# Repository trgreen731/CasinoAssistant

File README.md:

# The Odds Booster

This project is created by Marco Rojas, Jack Arndt, and Tim Green within UIUC ECE 445.

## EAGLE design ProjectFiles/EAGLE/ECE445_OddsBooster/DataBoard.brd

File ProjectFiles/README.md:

### File Type Notes
.dia files are used within the diagram software Dia

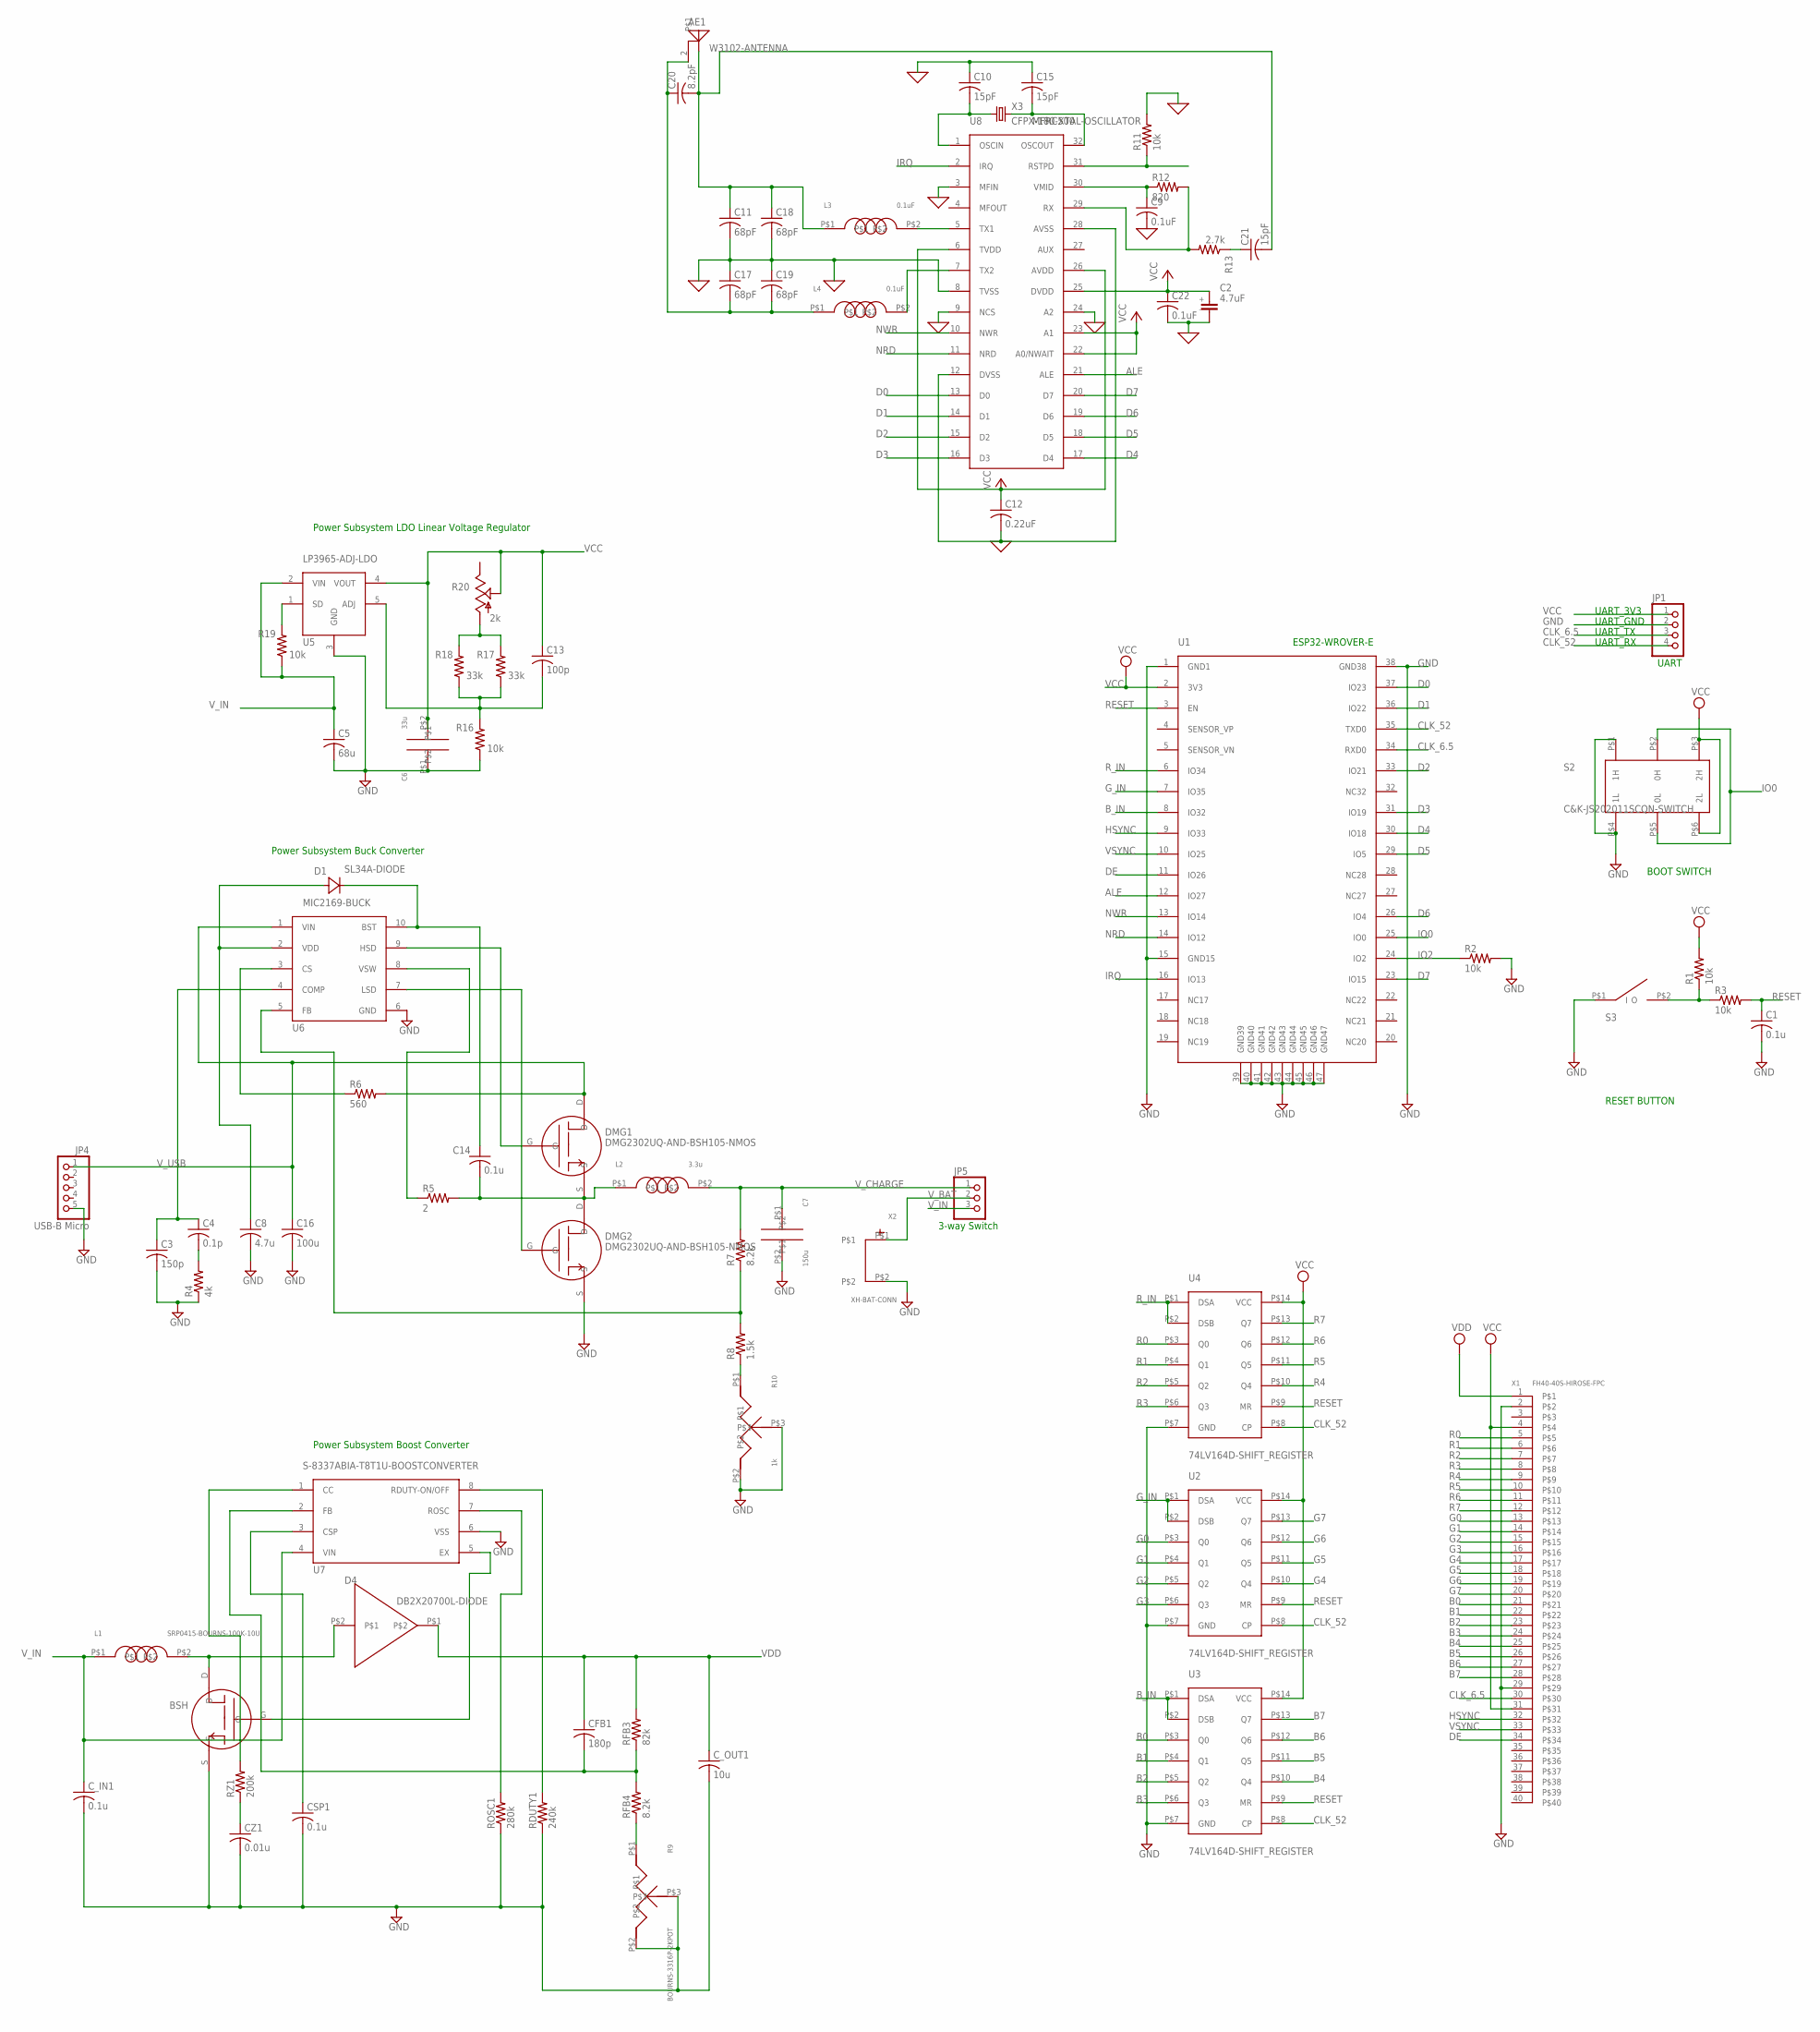
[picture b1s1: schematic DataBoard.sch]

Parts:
AE1: W3102-ANTENNA
BSH: DMG2302UQ-AND-BSH105-NMOS
C1, C14: 0.1u; C0805
C2: 4.7uF; 865080640004-ELECTROLYTIC-CAP
C3: 150p; C0805
C4: 0.1p; C0603
C5: 68u; C1206
C6: 33u; NEMCO-33U-TANT-CAP
C7: 150u; KEMET-T491-150U-TANT
C8: 4.7u; C0603
C9, C22: 0.1uF; C0805
C10, C15, C21: 15pF; C0805K
C11, C17, C18, C19: 68pF; C0805K
C12: 0.22uF; C0402
C13: 100p; C0805
C16: 100u; C1210
C20: 8.2pF; C0402
CFB1: 180p; C0805
CSP1: 0.1u; C0805
CZ1: 0.01u; C0805
C_IN1: 0.1u; C0805
C_OUT1: 10u; C0805
D1: SL34A-DIODE
D4: DB2X20700L-DIODE
DMG1, DMG2: DMG2302UQ-AND-BSH105-NMOS
JP1: PINHD-1X4; 1X04
JP4: USB-B Micro; 1X05
JP5: PINHD-1X3; 1X03
L1: SRP0415-BOURNS-100K-10U
L2: 3.3u; SRP0415-BOURNS-100K-10U
L3, L4: 0.1uF; SRP0415-BOURNS-100K-10U
R1, R2, R3, R11, R16, R19: 10k; R0805
R4: 4k; R0805
R5: 2; R0805
R6: 560; R0805
R7: 8.2k; R0805
R8: 1.5k; R0805
R9: BOURNS-3316P-2KPOT
R10: 1k; BOURNS-3316P-2KPOT
R12: 820; R0805
R13: 2.7k; R0805
R17, R18: 33k; R0805
R20: 2k; 3223G
RDUTY1: 240k; R0805
RFB3: 82k; R0805
RFB4: 8.2k; R0805
ROSC1: 280k; R0805
RZ1: 200k; R0805
S2: C&K-JS202011SCQN-SWITCH
S3: C&K-PTS636SL43SMTRLFS-PUSHBUTTON
U1: ESP32-WROVER-E
U2, U3, U4: 74LV164D-SHIFT_REGISTER
U5: LP3965-ADJ-LDO
U6: MIC2169-BUCK
U7: S-8337ABIA-T8T1U-BOOSTCONVERTER
U8: MFRC500
X1: FH40-40S-HIROSE-FPC
X2: XH-BAT-CONN
X3: CFPX-180-XTAL-OSCILLATOR

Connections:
0: C2.2- (2), C9.2, C10.1, C11.2, C12.2, C15.1, C17.1, C18.2, C19.1, C22.2, R11.2, U8.3 (MFIN), U8.8 (TVSS), U8.9 (NCS), U8.12 (DVSS), U8.24 (A2), U8.28 (AVSS)
ALE: U1.12 (IO27), U8.21 (ALE)
B0: U3.P$3 (Q0), X1.21
B1: U3.P$4 (Q1), X1.22
B2: U3.P$5 (Q2), X1.23
B3: U3.P$6 (Q3), X1.24
B4: U3.P$10 (Q4), X1.25
B5: U3.P$11 (Q5), X1.26
B6: U3.P$12 (Q6), X1.27
B7: U3.P$13 (Q7), X1.28
B_IN: U1.8 (IO32), U3.P$1 (DSA), U3.P$2 (DSB)
CLK_6.5: JP1.3, U1.34 (RXD0), X1.30
CLK_52: JP1.4, U1.35 (TXD0), U2.P$8 (CP), U3.P$8 (CP), U4.P$8 (CP)
D0: U1.37 (IO23), U8.13 (D0)
D1: U1.36 (IO22), U8.14 (D1)
D2: U1.33 (IO21), U8.15 (D2)
D3: U1.31 (IO19), U8.16 (D3)
D4: U1.30 (IO18), U8.17 (D4)
D5: U1.29 (IO5), U8.18 (D5)
D6: U1.26 (IO4), U8.19 (D6)
D7: U1.23 (IO15), U8.20 (D7)
DE: U1.11 (IO26), X1.34
EN: R1.1, R3.1, S3.P$2 (O)
G0: U2.P$3 (Q0), X1.13
G1: U2.P$4 (Q1), X1.14
G2: U2.P$5 (Q2), X1.15
G3: U2.P$6 (Q3), X1.16
G4: U2.P$10 (Q4), X1.17
G5: U2.P$11 (Q5), X1.18
G6: U2.P$12 (Q6), X1.19
G7: U2.P$13 (Q7), X1.20
GND: BSH.S, C1.2, C3.2, C5.2, C6.P$1, C7.P$2, C8.2, C16.2, CSP1.2, CZ1.2, C_IN1.2, C_OUT1.2, DMG2.S, JP1.2, JP4.5, R2.2, R4.1, R9.P$2, R9.P$3, R10.P$2, R10.P$3, R16.1, RDUTY1.1, ROSC1.1, S2.P$1 (1H), S2.P$4 (1L), S3.P$1 (I), U1.1 (GND1), U1.15 (GND15), U1.38 (GND38), U1.39 (GND39), U1.40 (GND40), U1.41 (GND41), U1.42 (GND42), U1.43 (GND43), U1.44 (GND44), U1.45 (GND45), U1.46 (GND46), U1.47 (GND47), U2.P$7 (GND), U3.P$7 (GND), U4.P$7 (GND), U5.3 (GND), U6.6 (GND), U7.6 (VSS), X1.2, X1.29, X2.P$2
G_IN: U1.7 (IO35), U2.P$1 (DSA), U2.P$2 (DSB)
HSYNC: U1.9 (IO33), X1.32
IO0: S2.P$2 (0H), S2.P$5 (0L), U1.25 (IO0)
IO2: R2.1, U1.24 (IO2)
IRQ: U1.16 (IO13), U8.2 (IRQ)
unnamed: C14.2, DMG1.S, DMG2.D, L2.P$1, R5.2
unnamed: C8.1, D1.1 (A), U6.2 (VDD)
unnamed: R5.1, U6.8 (VSW)
unnamed: C14.1, D1.2 (C), U6.10 (BST)
unnamed: C10.2, U8.1 (OSCIN), X3.1
unnamed: C15.2, U8.32 (OSCOUT), X3.3 (2)
unnamed: R11.1, U8.31 (RSTPD)
unnamed: C9.1, R12.1, U8.30 (VMID)
unnamed: R12.2, R13.2, U8.29 (RX)
unnamed: C21.1, R13.1
unnamed: L3.P$2, U8.5 (TX1)
unnamed: L4.P$2, U8.7 (TX2)
unnamed: AE1.1, C11.1, C18.1, C20.2, C21.2, L3.P$1
unnamed: AE1.2, C17.2, C19.2, C20.1, L4.P$1
unnamed: C13.2, R16.2, R17.1, R18.1, U5.5 (ADJ)
unnamed: R19.2, U5.1 (SD)
unnamed: R17.2, R18.2, R20.1 (A)
unnamed: DMG1.G, U6.9 (HSD)
unnamed: DMG2.G, U6.7 (LSD)
unnamed: R6.1, U6.3 (CS)
unnamed: C4.2, R4.2
unnamed: C3.1, C4.1, U6.4 (COMP)
unnamed: R7.1, R8.2, U6.5 (FB)
unnamed: R8.1, R10.P$1
unnamed: CSP1.1, U7.3 (CSP)
unnamed: BSH.G, U7.5 (EX)
unnamed: CZ1.1, RZ1.1
unnamed: RZ1.2, U7.1 (CC)
unnamed: CFB1.2, RFB3.1, RFB4.2, U7.2 (FB)
unnamed: ROSC1.2, U7.7 (ROSC)
unnamed: RDUTY1.2, U7.8 (RDUTY-ON/OFF)
unnamed: R9.P$1, RFB4.1
unnamed: BSH.D, D4.P$2, L1.P$2
NRD: U1.14 (IO12), U8.11 (NRD)
NWR: U1.13 (IO14), U8.10 (NWR)
R0: U4.P$3 (Q0), X1.5
R1: U4.P$4 (Q1), X1.6
R2: U4.P$5 (Q2), X1.7
R3: U4.P$6 (Q3), X1.8
R4: U4.P$10 (Q4), X1.9
R5: U4.P$11 (Q5), X1.10
R6: U4.P$12 (Q6), X1.11
R7: U4.P$13 (Q7), X1.12
RESET: C1.1, R3.2, U1.3 (EN), U2.P$9 (MR), U3.P$9 (MR), U4.P$9 (MR)
R_IN: U1.6 (IO34), U4.P$1 (DSA), U4.P$2 (DSB)
VCC: C2.1+ (1), C6.P$2, C12.1, C13.1, C22.1, JP1.1, R1.2, R20.2 (S), S2.P$3 (2H), S2.P$6 (2L), U1.2 (3V3), U2.P$14 (VCC), U3.P$14 (VCC), U4.P$14 (VCC), U5.4 (VOUT), U8.6 (TVDD), U8.22 (A0/NWAIT), U8.23 (A1), U8.25 (DVDD), U8.26 (AVDD), X1.4, X1.31
VDD: CFB1.1, C_OUT1.1, D4.P$1, RFB3.2, X1.1
VSYNC: U1.10 (IO25), X1.33
V_BAT: JP5.2, X2.P$1
V_CHARGE: C7.P$1, JP5.1, L2.P$2, R7.2
V_IN: C5.1, C_IN1.1, JP5.3, L1.P$1, R19.1, U5.2 (VIN), U7.4 (VIN)
V_USB: C16.1, DMG1.D, JP4.1, R6.2, U6.1 (VIN)

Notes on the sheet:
UART
RESET BUTTON
BOOT SWITCH
UART_RX
UART_TX
ESP32-WROVER-E
UART_3V3
UART_GND
Power Subsystem LDO Linear Voltage Regulator
Power Subsystem Buck Converter
Power Subsystem Boost Converter
3-way Switch

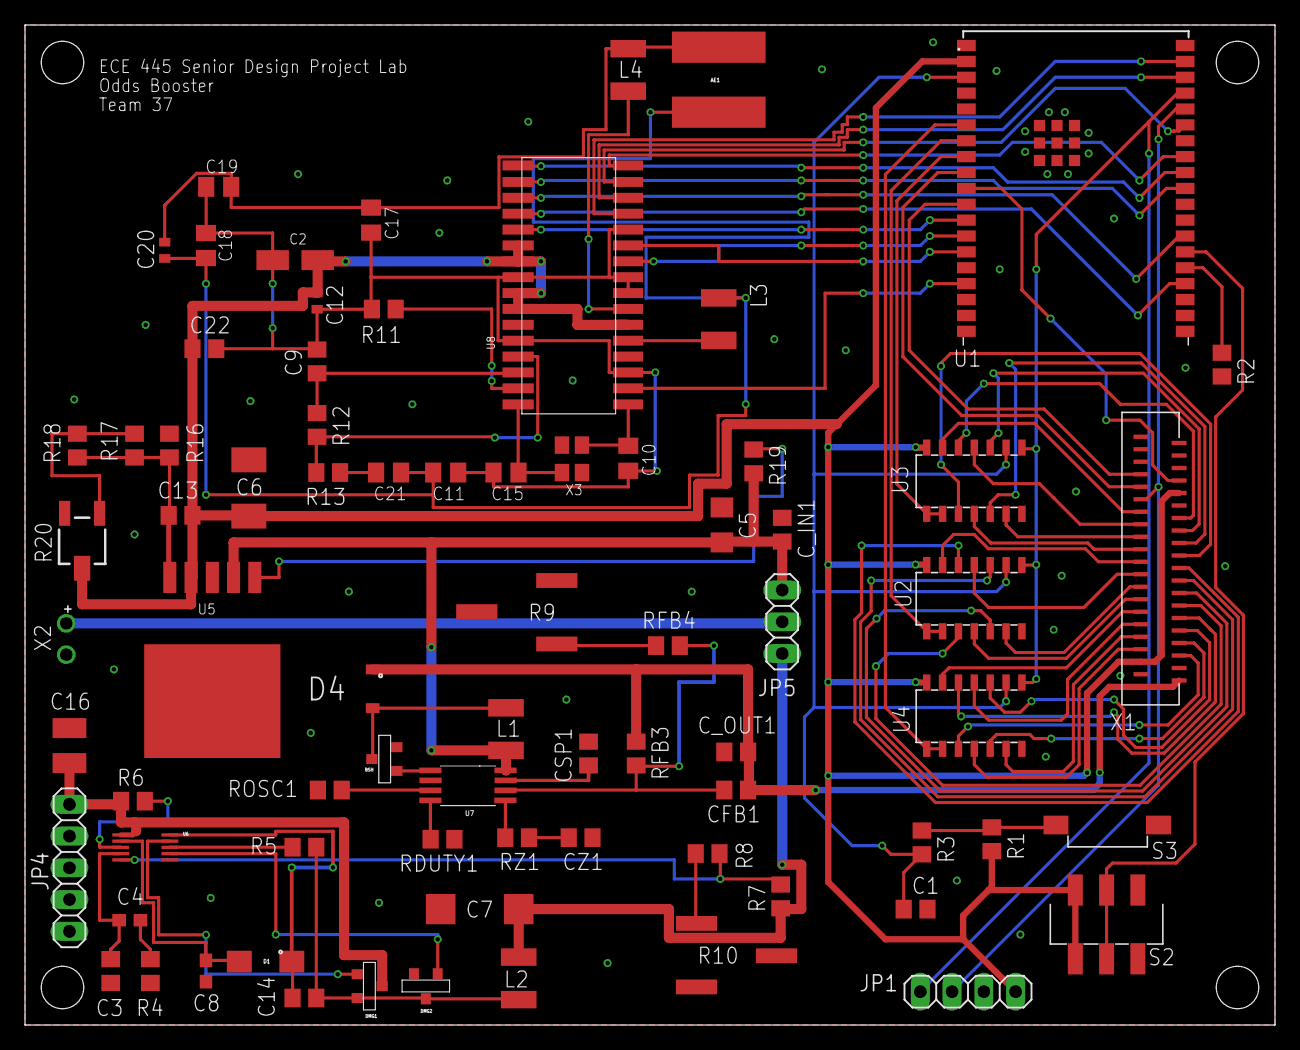
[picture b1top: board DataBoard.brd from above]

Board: 2 copper layers, 100.0 x 80.0 mm, 76 parts (0 on the bottom side), 89 nets.

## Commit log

2022-02-02 First commit, structure, notebooks, markdown readme files
2022-02-02 Added our RFA files to the projectfiles
2022-02-08 Gave dia files the file type, added proposal brainstorm to notebook
2022-02-08 Proposal Work Files
2022-02-08 Create OddsBoosterProposalRoughDraft
2022-02-08 Lab Notebook 2/8/2022: Proposal Brainstorming
2022-02-08 Create BlackjackStrategy
2022-02-08 Update BlackjackStrategy
2022-02-08 Rename BlackjackStrategy to BlackjackStrategy.md
2022-02-08 Rename OddsBoosterProposalRoughDraft to OddsBoosterProposalRoughDraft.txt
2022-02-08 Name change
2022-02-08 Rename OddsBoosterProposalRoughDraft.txt to OddsBoosterProposalRoughDraft.md
2022-02-08 Adding TA meeting notes
2022-02-08 notebook file names
2022-02-10 Started working on the proposal with a latex template for all future papers hopefully.
2022-02-10 First writing of the proposal introduction
2022-02-11 Proposal diagram and writing
2022-02-11 Finished design portion of proposal
2022-02-11 proposal done
2022-02-11 fixed refs
2022-02-14 2/14 Machine shop notes
2022-02-16 Component Search
2022-02-17 More RF components
2022-02-17 Power components
2022-02-18 New block diagram and design document template
2022-02-20 Finished schematic design for MCU, LCD, bluetooth
2022-02-21 comms, display
2022-02-22 RV table format
2022-02-22 Sample stuff for tomorrow
2022-02-24 Updating Notebook
2022-02-24 Changes to saved datasheets and new block diagram
2022-02-24 Boost converter data sheets and designs
2022-02-24 Data sheets
2022-02-25 Power Stuff
2022-02-25 smll changes
2022-02-25 stuff
2022-02-27 small changes to the design doc
2022-02-28 footprint work
2022-03-01 updated schematics, added eagle work with library and board work
2022-03-01 better design doc
2022-03-01 Comms and display layout
2022-03-01 ignore the eagle temp files
2022-03-01 layout minor changes
2022-03-08 updated data sheets and some layout changes
2022-03-09 footprints, schematic building, component checks
2022-03-09 Notebook Additions
2022-03-09 notebook notes and images
2022-03-09 Adding images and notes to notebook
2022-03-09 Making the images visible
2022-03-09 trying to get the gitignore to get rid of eagle intermediate files
2022-03-09 moved gitignore
2022-03-09 getting rid of cached backup eagle files and renaming folder so no spaces
2022-03-10 eagle updates
2022-03-10 team name
2022-03-11 PCB done along with generated gerber files
2022-03-14 Parts ordering instructions
2022-03-22 Updated PCB Gerber Files with .zip
2022-03-22 Update .gitignore to ignore MacOS system files
2022-04-04 Tim Green Progress Report
2022-04-04 App bluetooth examples
2022-04-04 MCU Bluetooth Samples (I might have messed up the gitignore for this one
2022-04-04 Notebook update
2022-04-20 working bluetooth mcu firmware, flash-able lcd mcu firmware, working bluetooth app debug and connection window
2022-04-20 removing a bunch of unneccessary stuff
2022-04-22 Layout for Notebook
2022-04-22 LCD updates
2022-04-23 LCD Info and MCU DRAM allocation Notebook Updates
2022-04-23 Options for internal memory space savings
2022-04-24 A long day of testing
2022-04-24 Blackjack Strategy Code
2022-04-25 the code for the lcd, bluetooth, and MFRC combined into a single file. the code for the bluetooth app connections
2022-04-25 testing evidence
2022-04-25 Update Notebook
2022-04-25 Notebook update with bluetooth LE pics
2022-04-25 soldering pic
2022-04-25 Power and MCU Bluetooth testing
2022-04-25 Notebook
2022-04-25 Video Links
2022-04-25 Small Change
2022-04-25 Ideas for demo
2022-04-25 Presentation Ideas
2022-05-01 input to output
2022-05-04 Notes for the presentation and final report
2022-05-04 Final Report, Presentation, images
2022-05-04 Some pictures
2022-05-04 screenshot
2022-05-04 Last pictures
2022-05-05 compressed powerpoint
2022-05-06 JackArndt Lab Notebook
